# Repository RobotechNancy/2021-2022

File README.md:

**`ROBOTECH 2021-2022`** 

## **`DÉPÔT OFFICIEL`**  ##

Dépot officiel 2021-2022 de l'équipe Robotech Nancy pour le projet Coupe de France de Robotique

Après de nombreuses années à explorer les quatre coins du monde et de l’univers, nos amis les robots ont

décidé d’aller explorer leur passé. En 2022, les robots iront fouiller les ruines d’une ancienne civilisation robo-
tique à la recherche des fragments oubliés de leurs origines.

Carré de fouille, trésors enterrés et statuettes sacrées, voilà ce qui attend nos archéologues chevronnés, et
rien ne les arrêtera dans la quête de leur Histoire.
Alors sortez les pelles et les pioches, car l’aventure nous attend !

## **`Devise :`** ##
*L’utilsation optimale de l’énergie est une base élémentaire
dans l’ensemble de nos conceptions.
Savoir optimiser l’utilisation des robots existant ne nous satisfait pas.
Nous voulons apprendre à concevoir les robots de demain
utilisant des technologies novatrices ainsi qu’une 
intelligence réelle supportée par une électronique et une informatique de haut niveau.*

Nos objectifs de cette année sont :

- Construire les 2 robots nécessaires dans la version 2022 de la compétition.
- Consolider la structuration en blocs fonctionnels indépendants ( Base roulante, Odométrie, partie robotique annuelle spécifique, Introduction des services de maintenance, … ).
- Rendre les codes informatiques d’un très haut niveau de qualité ( Méthodologique, Fiables ( traitant de toutes erreurs), réelle documentation professionnelle, … ).
- Cette année nous souhaitons introduire les Graphes et moteur de Graphe afin de rendre plus facile et fiable les évolutions de la compétition tant pour cette année et surtout les années à venir.
- Introduire l’utilisation des technologies WEB dans les logiciels d’Interface Homme Robot.
- Consolider les communications hertziennes entre nos deux robots collaboratifs afin d’introduire l'immunité aux attaques de cyber-sécurité.

## **`EQUIPE DE L'ANNEE 2021-2022`**  ##

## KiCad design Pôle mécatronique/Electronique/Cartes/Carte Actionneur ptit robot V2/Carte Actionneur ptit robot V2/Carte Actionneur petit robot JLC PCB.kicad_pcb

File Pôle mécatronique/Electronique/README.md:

TO DO List:
- Base roulante
	- Cablage temp vers nucléo
	- Teste régulateur
	
- Système TOF
	- Teste des capteurs
	
- Bloc alimentation
	- Dimensionnement de la batterie
	- Dimensionnement du BMS
	- Dimensionnement du régulateur

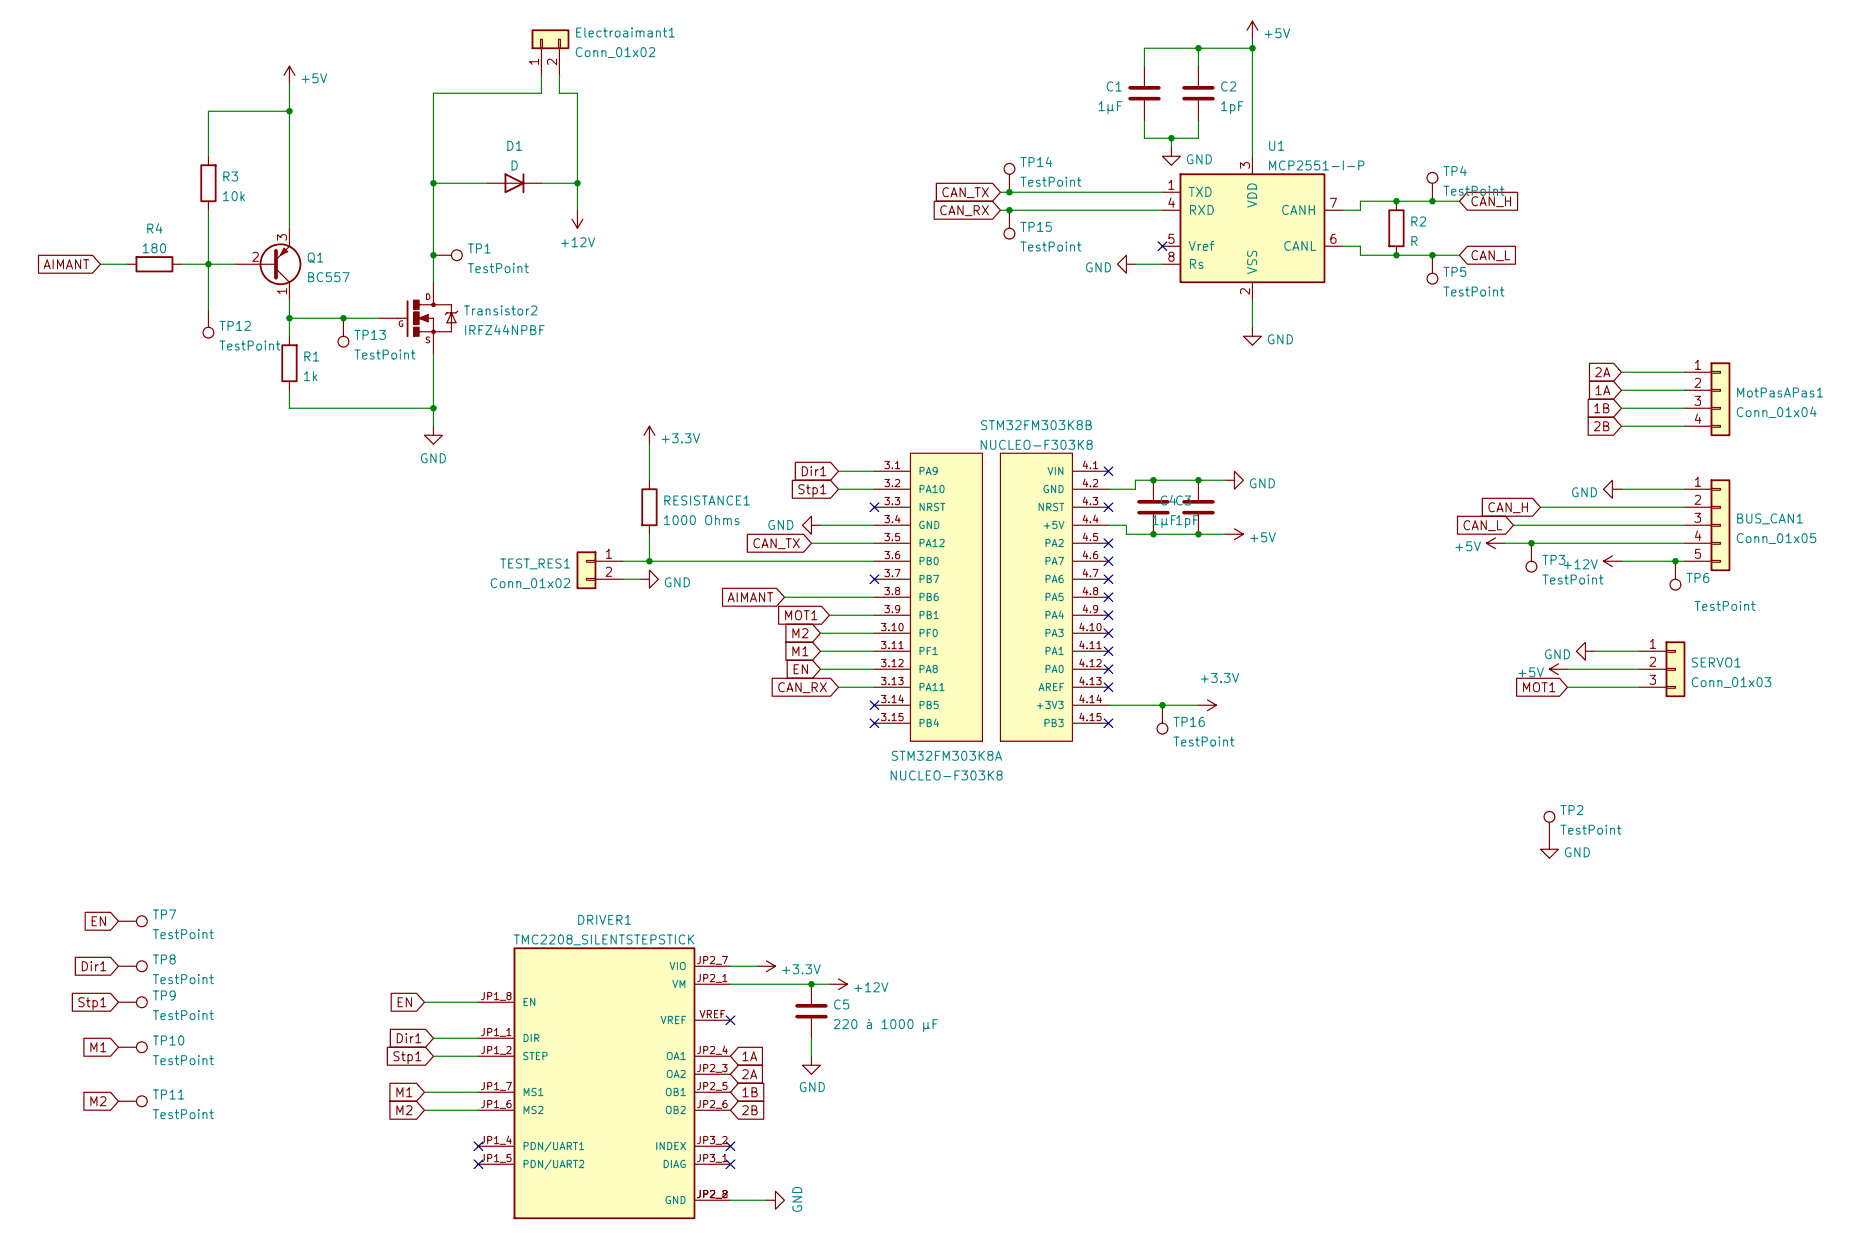
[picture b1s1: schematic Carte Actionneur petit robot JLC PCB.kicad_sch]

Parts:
BUS_CAN1: Conn_01x05; JST_PH_B5B-PH-K_1x05_P2.00mm_Vertical
C1, C4: 1µF; C_1206_3216Metric
C2, C3: 1pF; C_1206_3216Metric
C5: 220 à 1000 µF; CP_Radial_D8.0mm_P3.50mm
D1: D; D_A-405_P12.70mm_Horizontal
DRIVER1: TMC2208_SILENTSTEPSTICK; MODULE_TMC2208_SILENTSTEPSTICK
Electroaimant1: Conn_01x02; JST_PH_B2B-PH-K_1x02_P2.00mm_Vertical
MotPasAPas1: Conn_01x04; PinSocket_1x04_P2.54mm_Vertical
Q1: BC557; TO-92_Inline
R1: 1k; R_Axial_DIN0207_L6.3mm_D2.5mm_P10.16mm_Horizontal
R2: R; R_Axial_DIN0207_L6.3mm_D2.5mm_P10.16mm_Horizontal
R3: 10k; R_Axial_DIN0207_L6.3mm_D2.5mm_P10.16mm_Horizontal
R4: 180; R_Axial_DIN0207_L6.3mm_D2.5mm_P10.16mm_Horizontal
RESISTANCE1: 1000 Ohms; R_Axial_DIN0207_L6.3mm_D2.5mm_P10.16mm_Horizontal
SERVO1: Conn_01x03; JST_PH_B3B-PH-K_1x03_P2.00mm_Vertical
STM32FM303K8: NUCLEO-F303K8; iou; PARTREV 3
TEST_RES1: Conn_01x02; PinSocket_1x02_P2.54mm_Vertical
TP1, TP2, TP3, TP4, TP5, TP6, TP7, TP8, TP9, TP10, TP11, TP12, TP13, TP14, TP15, TP16: TestPoint; TestPoint_Pad_D2.0mm
Transistor2: IRFZ44NPBF; TO-220-3_Horizontal_TabDown
U1: MCP2551-I-P; DIP-8_W7.62mm

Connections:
1A: DRIVER1.JP2_4 (OA1), MotPasAPas1.2
1B: DRIVER1.JP2_5 (OB1), MotPasAPas1.3
2A: DRIVER1.JP2_3 (OA2), MotPasAPas1.1
2B: DRIVER1.JP2_6 (OB2), MotPasAPas1.4
+3V3: DRIVER1.JP2_7 (VIO), RESISTANCE1.1, STM32FM303K8.4.14 (+3V3), TP16.1
+5V: BUS_CAN1.4, C1.1, C2.1, C3.2, C4.2, Q1.3 (E), R3.2, SERVO1.2, STM32FM303K8.4.4 (+5V), TP3.1, U1.3 (VDD)
+12V: BUS_CAN1.5, C5.1, D1.1 (K), DRIVER1.JP2_1 (VM), Electroaimant1.2, TP6.1
AIMANT: R4.2, STM32FM303K8.3.8 (PB6)
CAN_H: BUS_CAN1.2, R2.1, TP4.1, U1.7 (CANH)
CAN_L: BUS_CAN1.3, R2.2, TP5.1, U1.6 (CANL)
CAN_RX: STM32FM303K8.3.13 (PA11), TP15.1, U1.4 (RXD)
CAN_TX: STM32FM303K8.3.5 (PA12), TP14.1, U1.1 (TXD)
Dir1: DRIVER1.JP1_1 (DIR), STM32FM303K8.3.1 (PA9), TP8.1
EN: DRIVER1.JP1_8 (EN), STM32FM303K8.3.12 (PA8), TP7.1
GND: BUS_CAN1.1, C1.2, C2.2, C3.1, C4.1, C5.2, DRIVER1.JP2_2 (GND), DRIVER1.JP2_8 (GND), R1.1, SERVO1.1, STM32FM303K8.3.4 (GND), STM32FM303K8.4.2 (GND), TEST_RES1.2, TP2.1, Transistor2.3, U1.2 (VSS), U1.8 (Rs)
M1: DRIVER1.JP1_7 (MS1), STM32FM303K8.3.11 (PF1), TP10.1
M2: DRIVER1.JP1_6 (MS2), STM32FM303K8.3.10 (PF0), TP11.1
MOT1: SERVO1.3, STM32FM303K8.3.9 (PB1)
unnamed: D1.2 (A), Electroaimant1.1, TP1.1, Transistor2.2
unnamed: Q1.1 (C), R1.2, TP13.1, Transistor2.1
unnamed: Q1.2 (B), R3.1, R4.1, TP12.1
unnamed: RESISTANCE1.2, STM32FM303K8.3.6 (PB0), TEST_RES1.1
Stp1: DRIVER1.JP1_2 (STEP), STM32FM303K8.3.2 (PA10), TP9.1

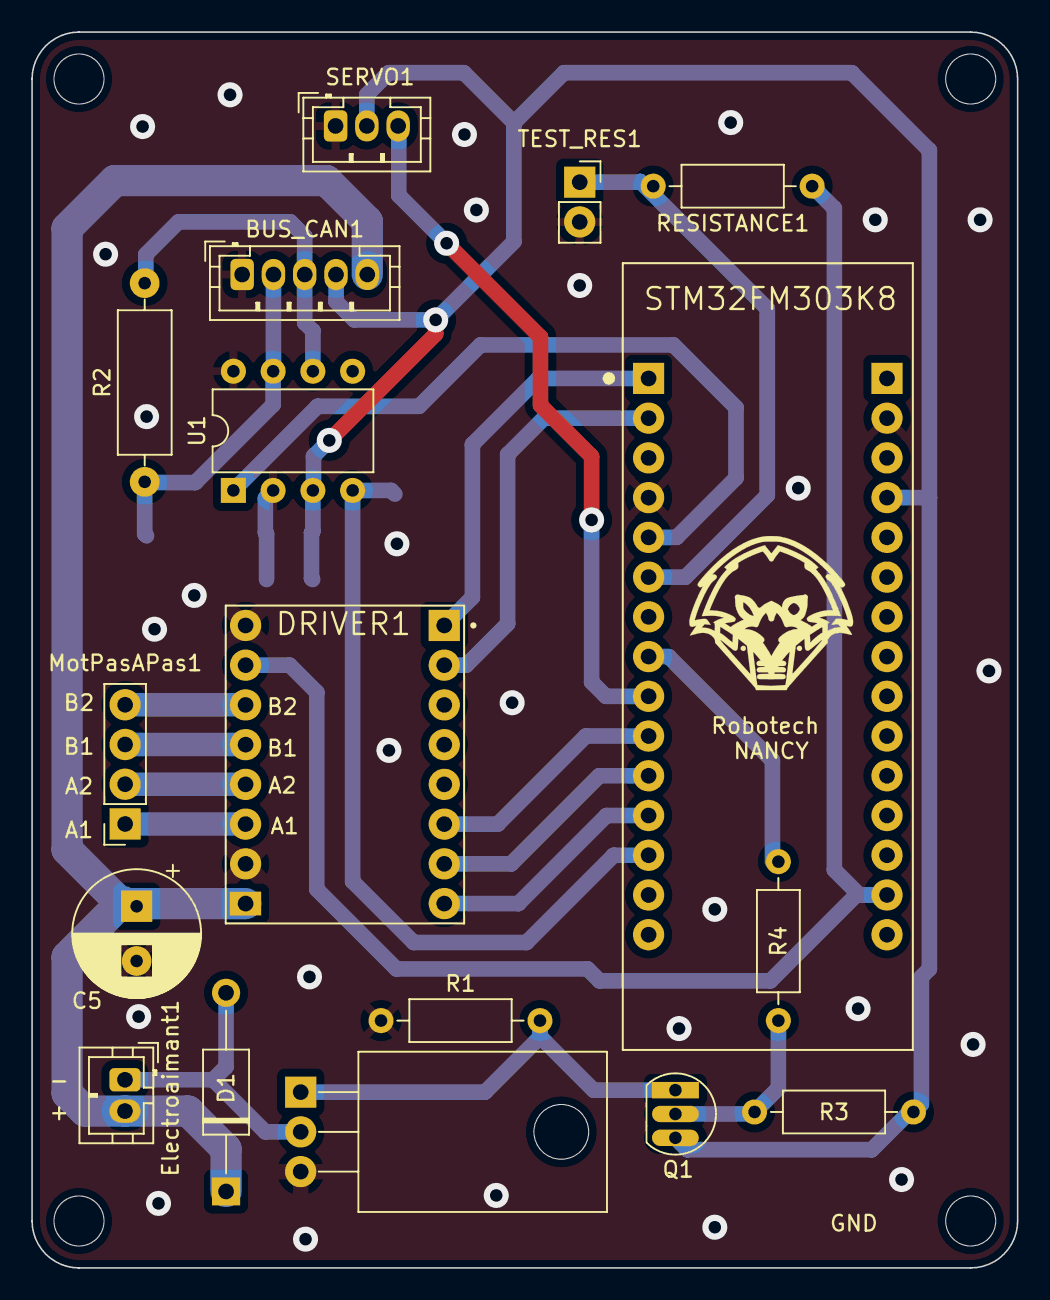
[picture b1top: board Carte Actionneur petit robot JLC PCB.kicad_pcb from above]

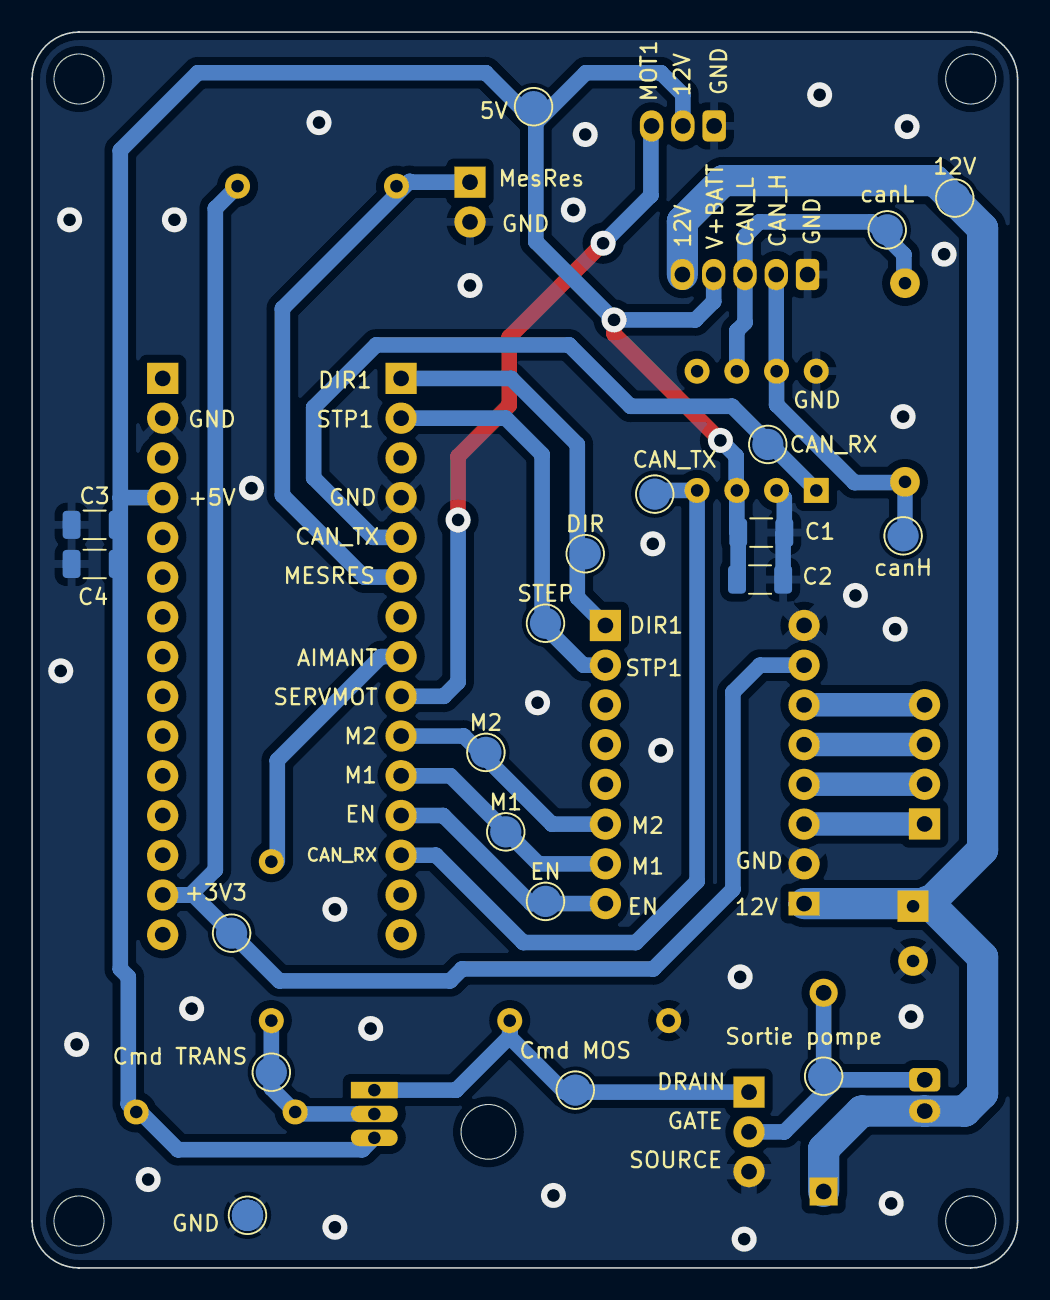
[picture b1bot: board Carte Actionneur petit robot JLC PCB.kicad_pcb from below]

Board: 2 copper layers, 63.0 x 79.0 mm, 37 parts (20 on the bottom side), 23 nets.

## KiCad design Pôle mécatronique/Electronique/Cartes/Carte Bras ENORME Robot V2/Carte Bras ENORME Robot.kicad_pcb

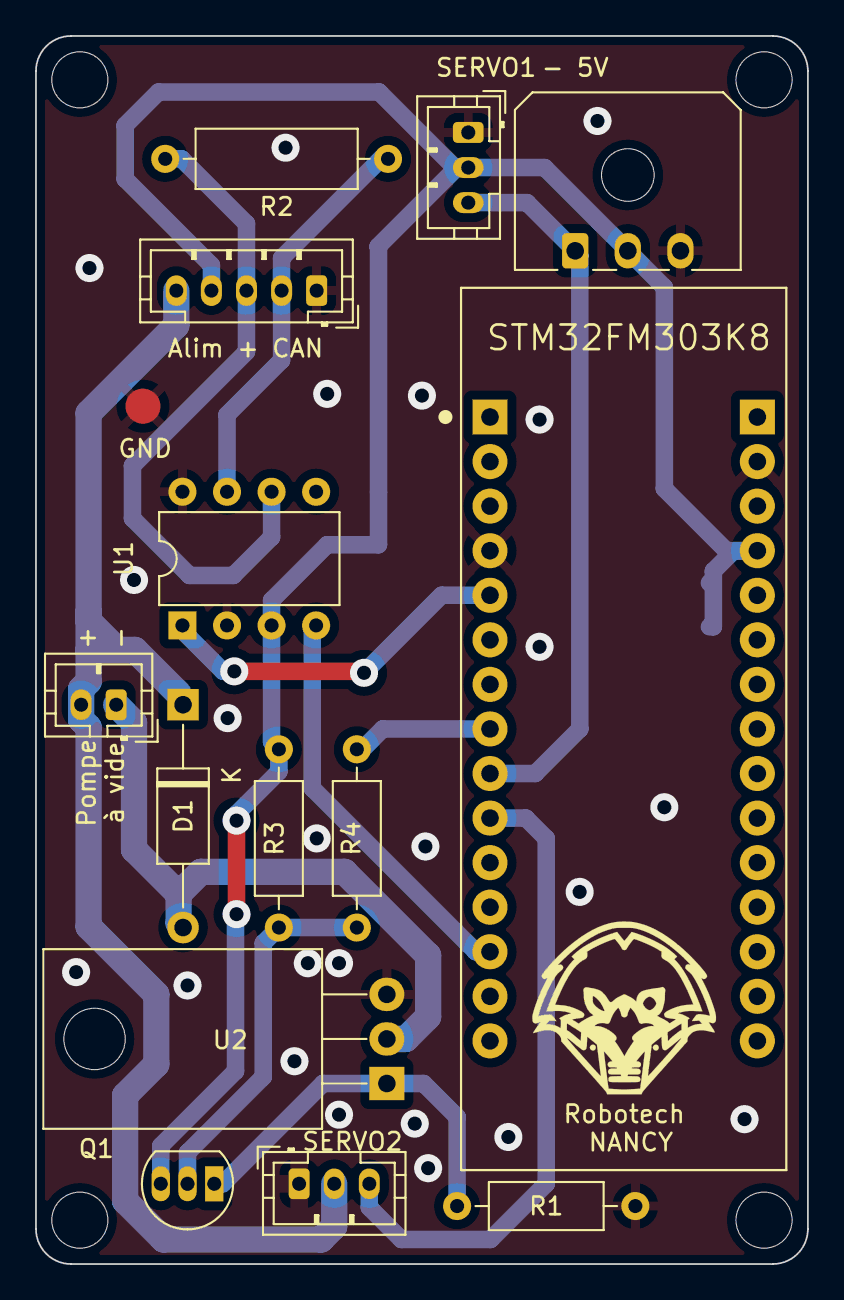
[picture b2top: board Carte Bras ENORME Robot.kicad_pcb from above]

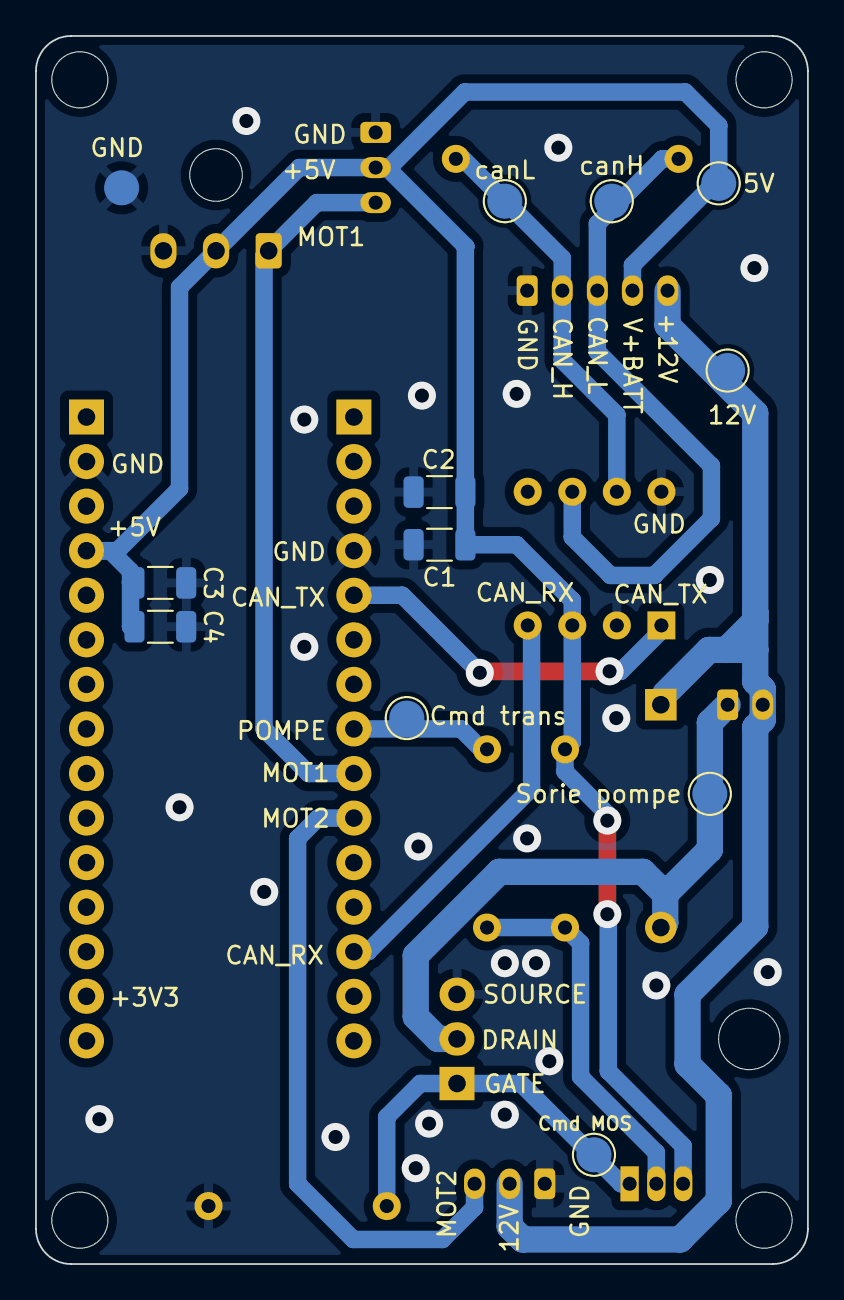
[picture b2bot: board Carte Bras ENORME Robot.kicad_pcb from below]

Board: 2 copper layers, 44.0 x 70.0 mm, 25 parts (11 on the bottom side), 13 nets.

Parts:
BUS_CAN1: Conn_01x05; JST_PH_B5B-PH-K_1x05_P2.00mm_Vertical
C1, C2, C3, C4: C; C_1206_3216Metric
D1: D; D_A-405_P12.70mm_Horizontal
JS1: Molex_Micro-Fit_3.0_43650-0300_1x03_P3.00mm_Horiz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; Molex_Micro-Fit_3.0_43650-0300_1x03_P3.00mm_Horizontal
PompeAVide1: Conn_01x02; JST_PH_B2B-PH-K_1x02_P2.00mm_Vertical
Q1: BC557; TO-92_Inline
R1: 1k; R_Axial_DIN0207_L6.3mm_D2.5mm_P10.16mm_Horizontal
R2: R; R_Axial_DIN0309_L9.0mm_D3.2mm_P12.70mm_Horizontal
R3: 10k; R_Axial_DIN0207_L6.3mm_D2.5mm_P10.16mm_Horizontal
R4: 180; R_Axial_DIN0207_L6.3mm_D2.5mm_P10.16mm_Horizontal
SERVO1, SERVO2: Conn_01x03; JST_PH_B3B-PH-K_1x03_P2.00mm_Vertical
STM32FM303K8: NUCLEO-F303K8; MODULE_NUCLEO-F303K8
TP2, TP3, TP4, TP5, TP6, TP7, TP8: TestPoint; TestPoint_Pad_D2.0mm
U1: MCP2551-I-P; DIP-8_W7.62mm
U2: IRFZ44NPBF; TO-220-3_Horizontal_TabDown

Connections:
+5V: BUS_CAN1.4, C1.1, C2.1, C3.2, C4.2, JS1.2, Q1.3 (E), R3.1, SERVO1.2, STM32FM303K8.4.4 (+5V), TP3.1, U1.3 (VDD)
+12V: BUS_CAN1.5, D1.1 (K), PompeAVide1.2, SERVO2.2, TP6.1
CAN_H: BUS_CAN1.2, R2.1, TP4.1, U1.7 (CANH)
CAN_L: BUS_CAN1.3, R2.2, TP5.1, U1.6 (CANL)
CAN_RX: STM32FM303K8.3.13 (PA11), U1.4 (RXD)
CAN_TX: STM32FM303K8.3.5 (PA12), U1.1 (TXD)
GND: BUS_CAN1.1, C1.2, C2.2, C3.1, C4.1, JS1.3, R1.2, SERVO1.1, SERVO2.1, STM32FM303K8.3.4 (GND), STM32FM303K8.4.2 (GND), U1.2 (VSS), U1.8 (Rs), U2.3
MOT1: JS1.1, SERVO1.3, STM32FM303K8.3.9 (PB1)
MOT2: SERVO2.3, STM32FM303K8.3.10 (PF0)
unnamed: D1.2 (A), PompeAVide1.1, TP2.1, U2.2
unnamed: Q1.1 (C), R1.1, TP8.1, U2.1
unnamed: Q1.2 (B), R3.2, R4.2
POMPE: R4.1, STM32FM303K8.3.8 (PB6), TP7.1

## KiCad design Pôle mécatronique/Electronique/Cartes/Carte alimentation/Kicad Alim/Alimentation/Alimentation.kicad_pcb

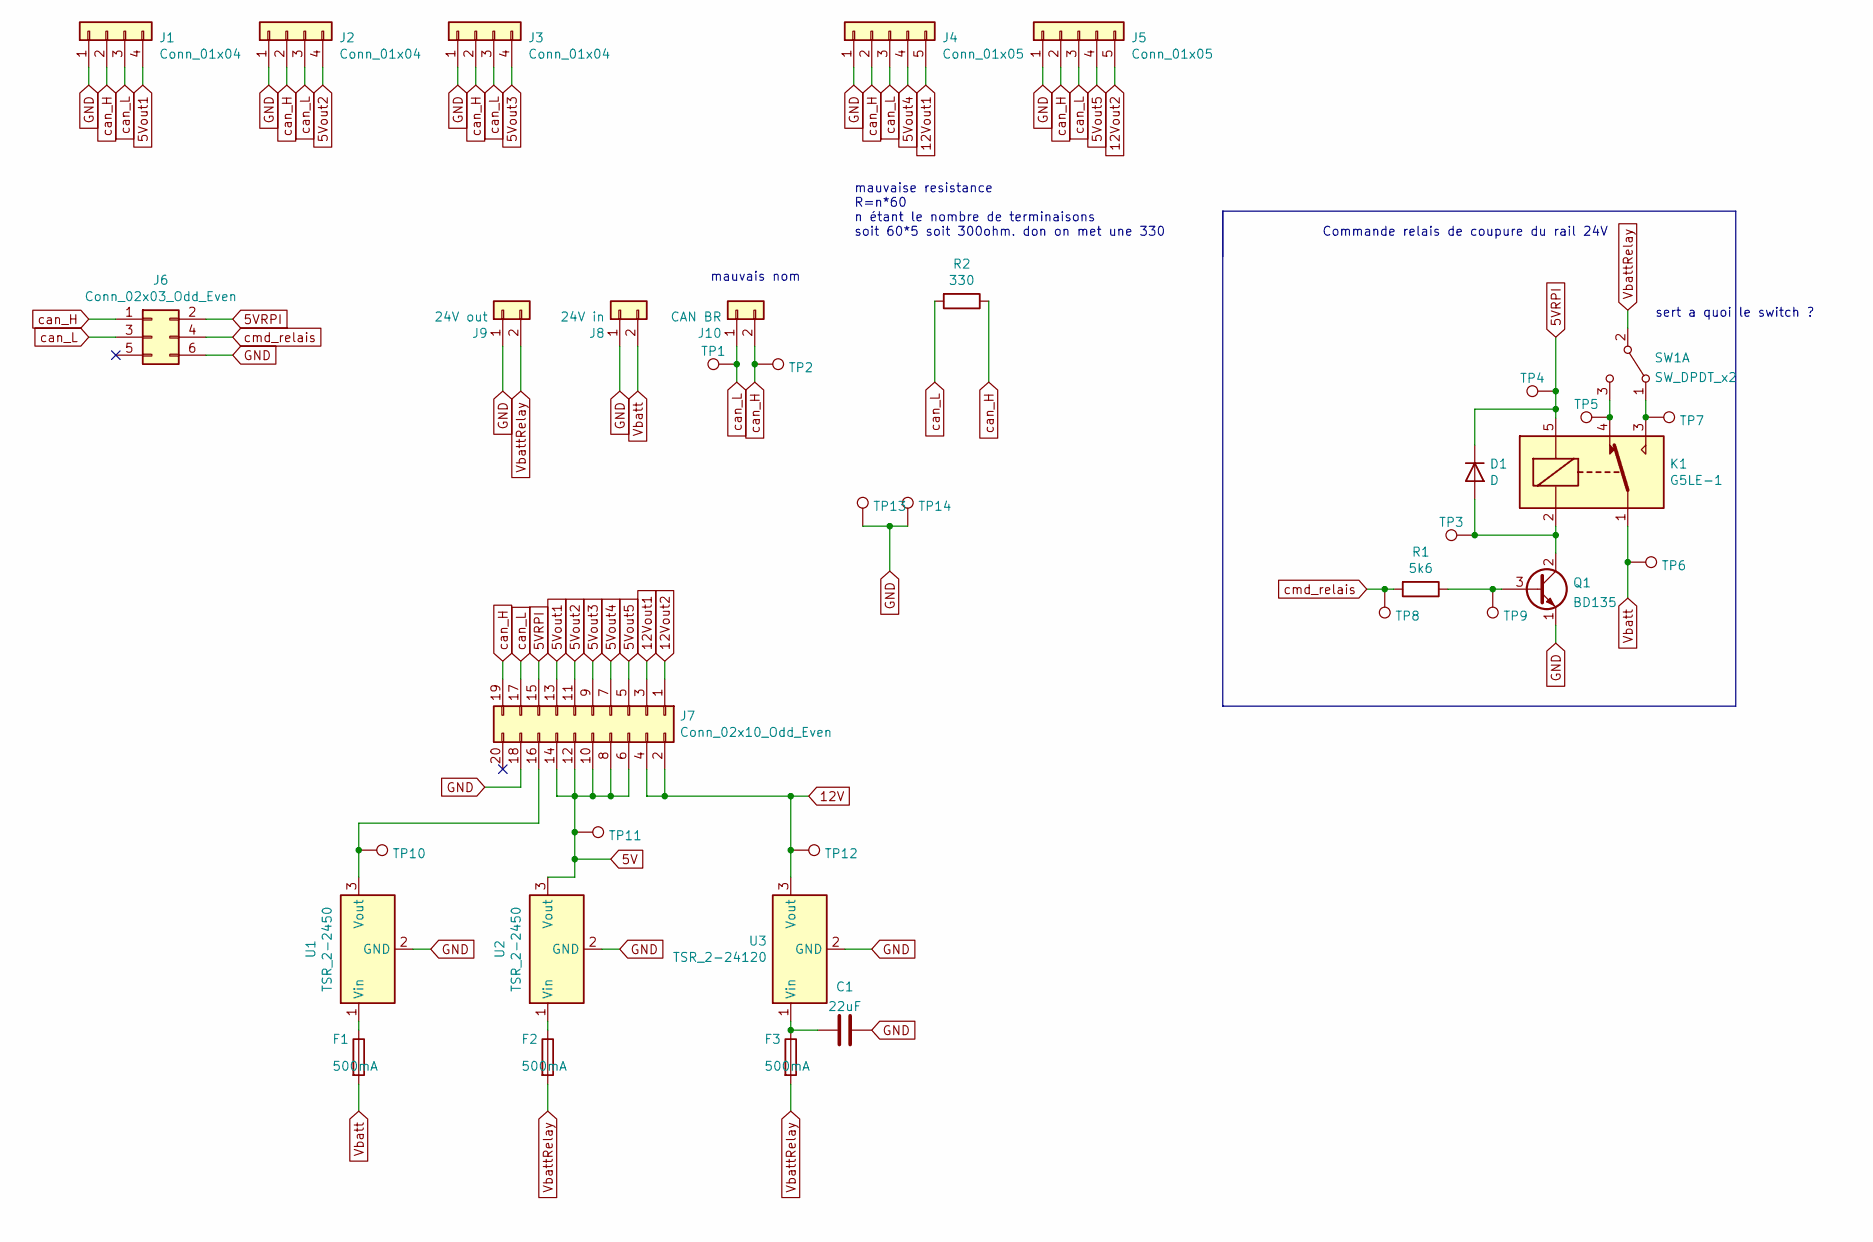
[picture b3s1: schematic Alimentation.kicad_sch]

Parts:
C1: 22uF; CP_Radial_D5.0mm_P2.00mm
D1: D; D_DO-15_P12.70mm_Horizontal
F1, F2, F3: 500mA; Fuse_BelFuse_0ZRE0012FF_L8.3mm_W3.8mm
J1, J2, J3: Conn_01x04; JST_PH_B4B-PH-K_1x04_P2.00mm_Vertical
J4, J5: Conn_01x05; JST_PH_B5B-PH-K_1x05_P2.00mm_Vertical
J6: Conn_02x03_Odd_Even; Hirose_DF11-6DP-2DSA_2x03_P2.00mm_Vertical
J7: Conn_02x10_Odd_Even; PinSocket_2x10_P2.54mm_Vertical
J8: 24V in; AMASS_XT60-F_1x02_P7.20mm_Vertical
J9: 24V out; AMASS_XT60-F_1x02_P7.20mm_Vertical
J10: CAN BR; JST_PH_B2B-PH-K_1x02_P2.00mm_Vertical
K1: G5LE-1; Relay_SPDT_Omron-G5LE-1
Q1: BD135; TO-126-3_Vertical
R1: 5k6; R_Axial_DIN0207_L6.3mm_D2.5mm_P10.16mm_Horizontal
R2: 330; R_Axial_DIN0207_L6.3mm_D2.5mm_P10.16mm_Horizontal
SW1: SW_DPDT_x2; Switch_3_Pin
TP1, TP2, TP3, TP4, TP5, TP6, TP7, TP8, TP9, TP10, TP11, TP12, TP13, TP14: TestPoint; TestPoint_Pad_D2.0mm
U1, U2: TSR_2-2450; Converter_DCDC_TRACO_TSR-1_THT
U3: TSR_2-24120; Converter_DCDC_TRACO_TSR-1_THT

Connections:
5V: J7.6, J7.8, J7.10, J7.12, J7.14, TP11.1, U2.3 (Vout)
5VRPI: D1.1 (K), J6.2, J7.15, K1.5, TP4.1
5Vout1: J1.4, J7.13
5Vout2: J2.4, J7.11
5Vout3: J3.4, J7.9
5Vout4: J4.4, J7.7
5Vout5: J5.4, J7.5
12V: J7.2, J7.4, TP12.1, U3.3 (Vout)
12Vout1: J4.5, J7.3
12Vout2: J5.5, J7.1
GND: C1.2, J1.1, J2.1, J3.1, J4.1, J5.1, J6.6, J7.18, J8.1, J9.1, Q1.1 (E), TP13.1, TP14.1, U1.2 (GND), U2.2 (GND), U3.2 (GND)
unnamed: C1.1, F3.1, U3.1 (Vin)
unnamed: D1.2 (A), K1.2, Q1.2 (C), TP3.1
unnamed: F1.1, U1.1 (Vin)
unnamed: F2.1, U2.1 (Vin)
unnamed: J7.16, TP10.1, U1.3 (Vout)
unnamed: K1.3, SW1.1 (A), TP7.1
unnamed: K1.4, SW1.3 (C), TP5.1
unnamed: Q1.3 (B), R1.1, TP9.1
Vbatt: F1.2, J8.2, K1.1, TP6.1
VbattRelay: F2.2, F3.2, J9.2, SW1.2 (B)
can_H: J1.2, J2.2, J3.2, J4.2, J5.2, J6.1, J7.19, J10.2, R2.1, TP2.1
can_L: J1.3, J2.3, J3.3, J4.3, J5.3, J6.3, J7.17, J10.1, R2.2, TP1.1
cmd_relais: J6.4, R1.2, TP8.1

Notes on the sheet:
Commande relais de coupure du rail 24V
mauvaise resistance R=n*60 n étant le nombre de terminaisons soit 60*5 soit 300ohm. don on met une 330
sert a quoi le switch ?
mauvais nom

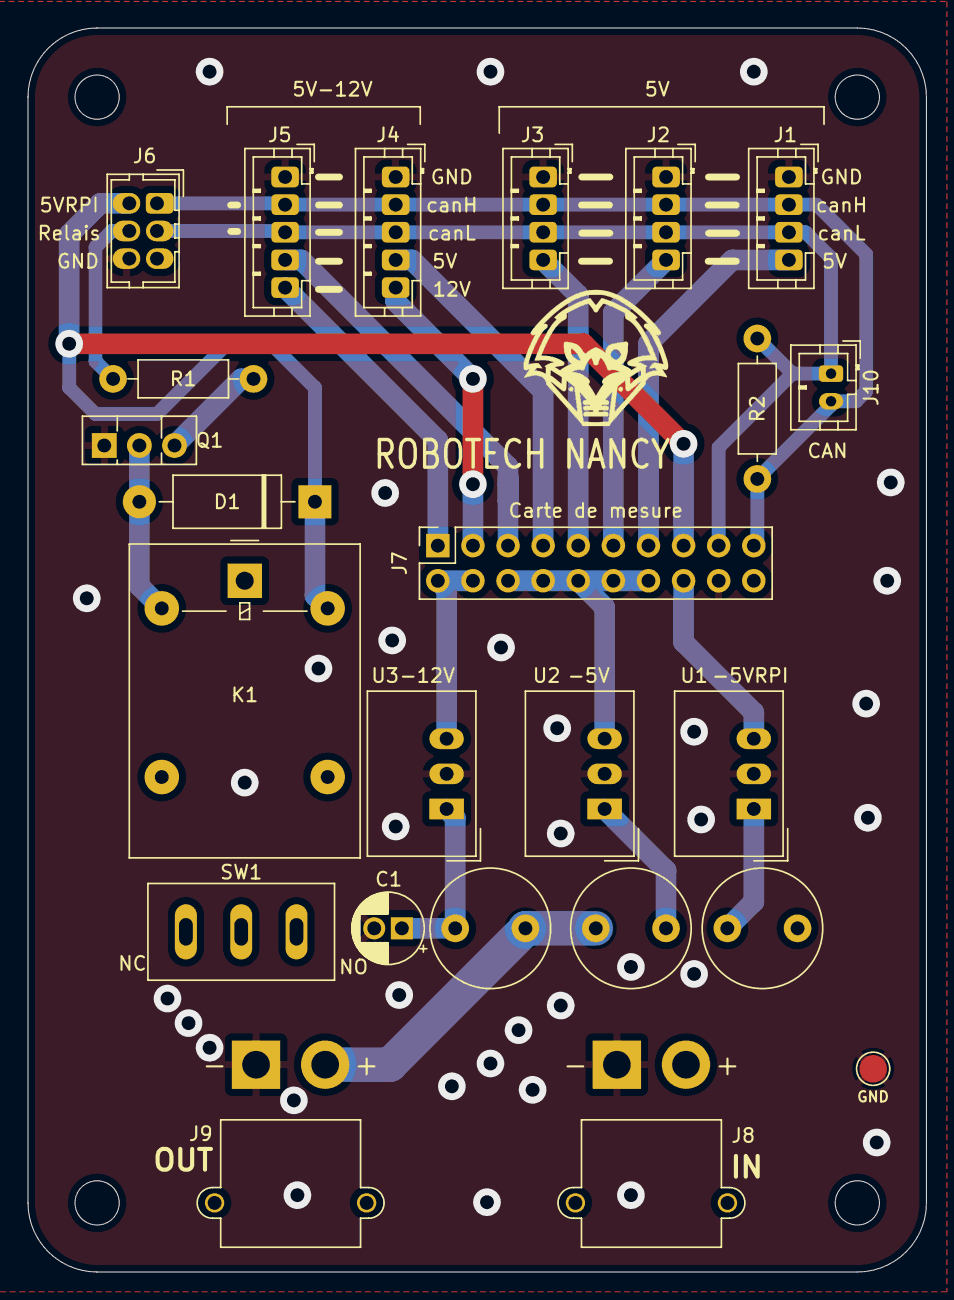
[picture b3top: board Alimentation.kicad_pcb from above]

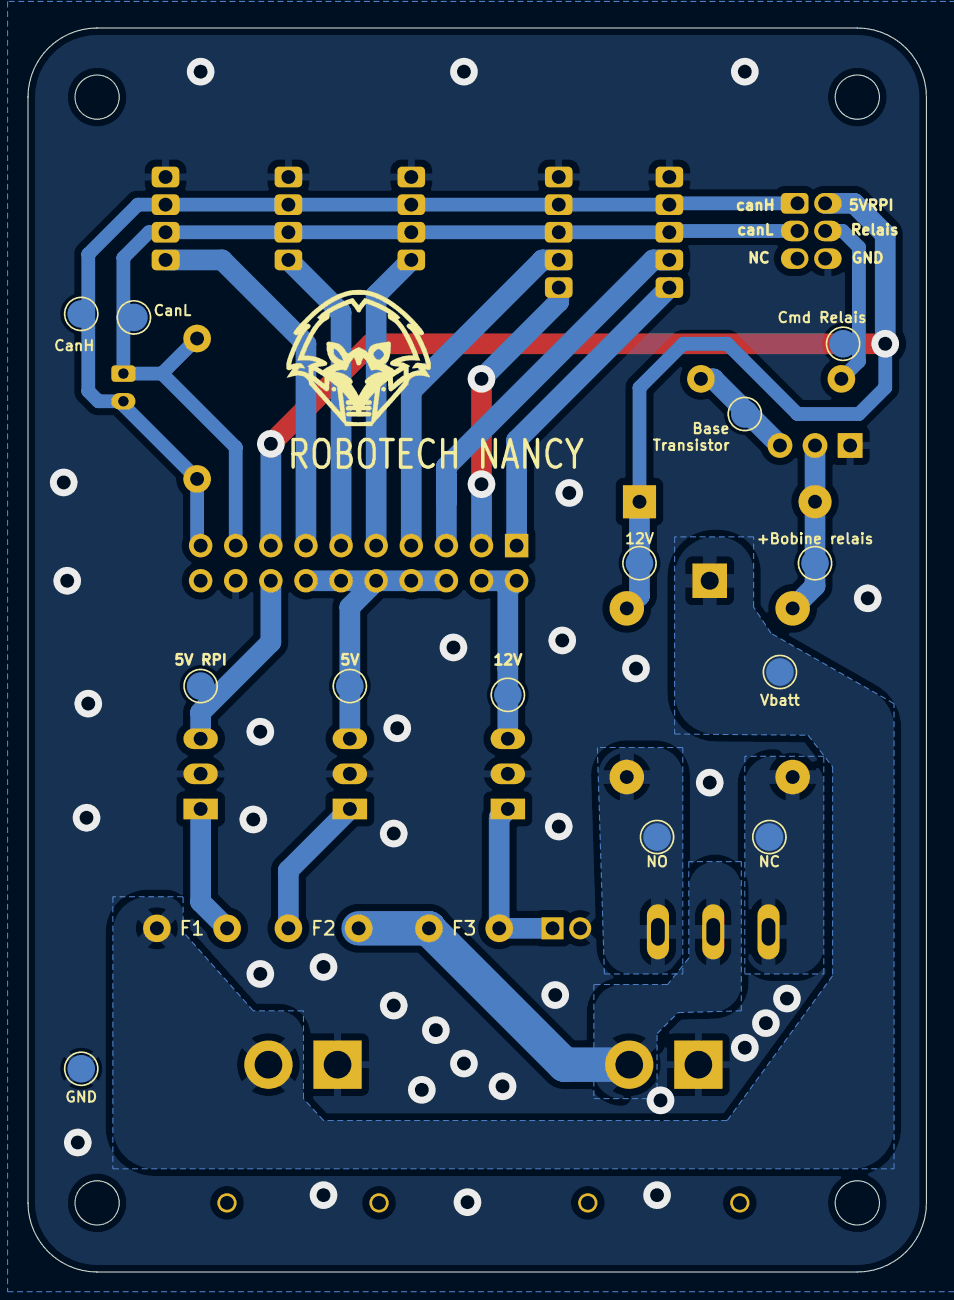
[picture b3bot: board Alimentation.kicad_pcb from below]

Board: 2 copper layers, 65.0 x 90.0 mm, 37 parts (13 on the bottom side), 24 nets.

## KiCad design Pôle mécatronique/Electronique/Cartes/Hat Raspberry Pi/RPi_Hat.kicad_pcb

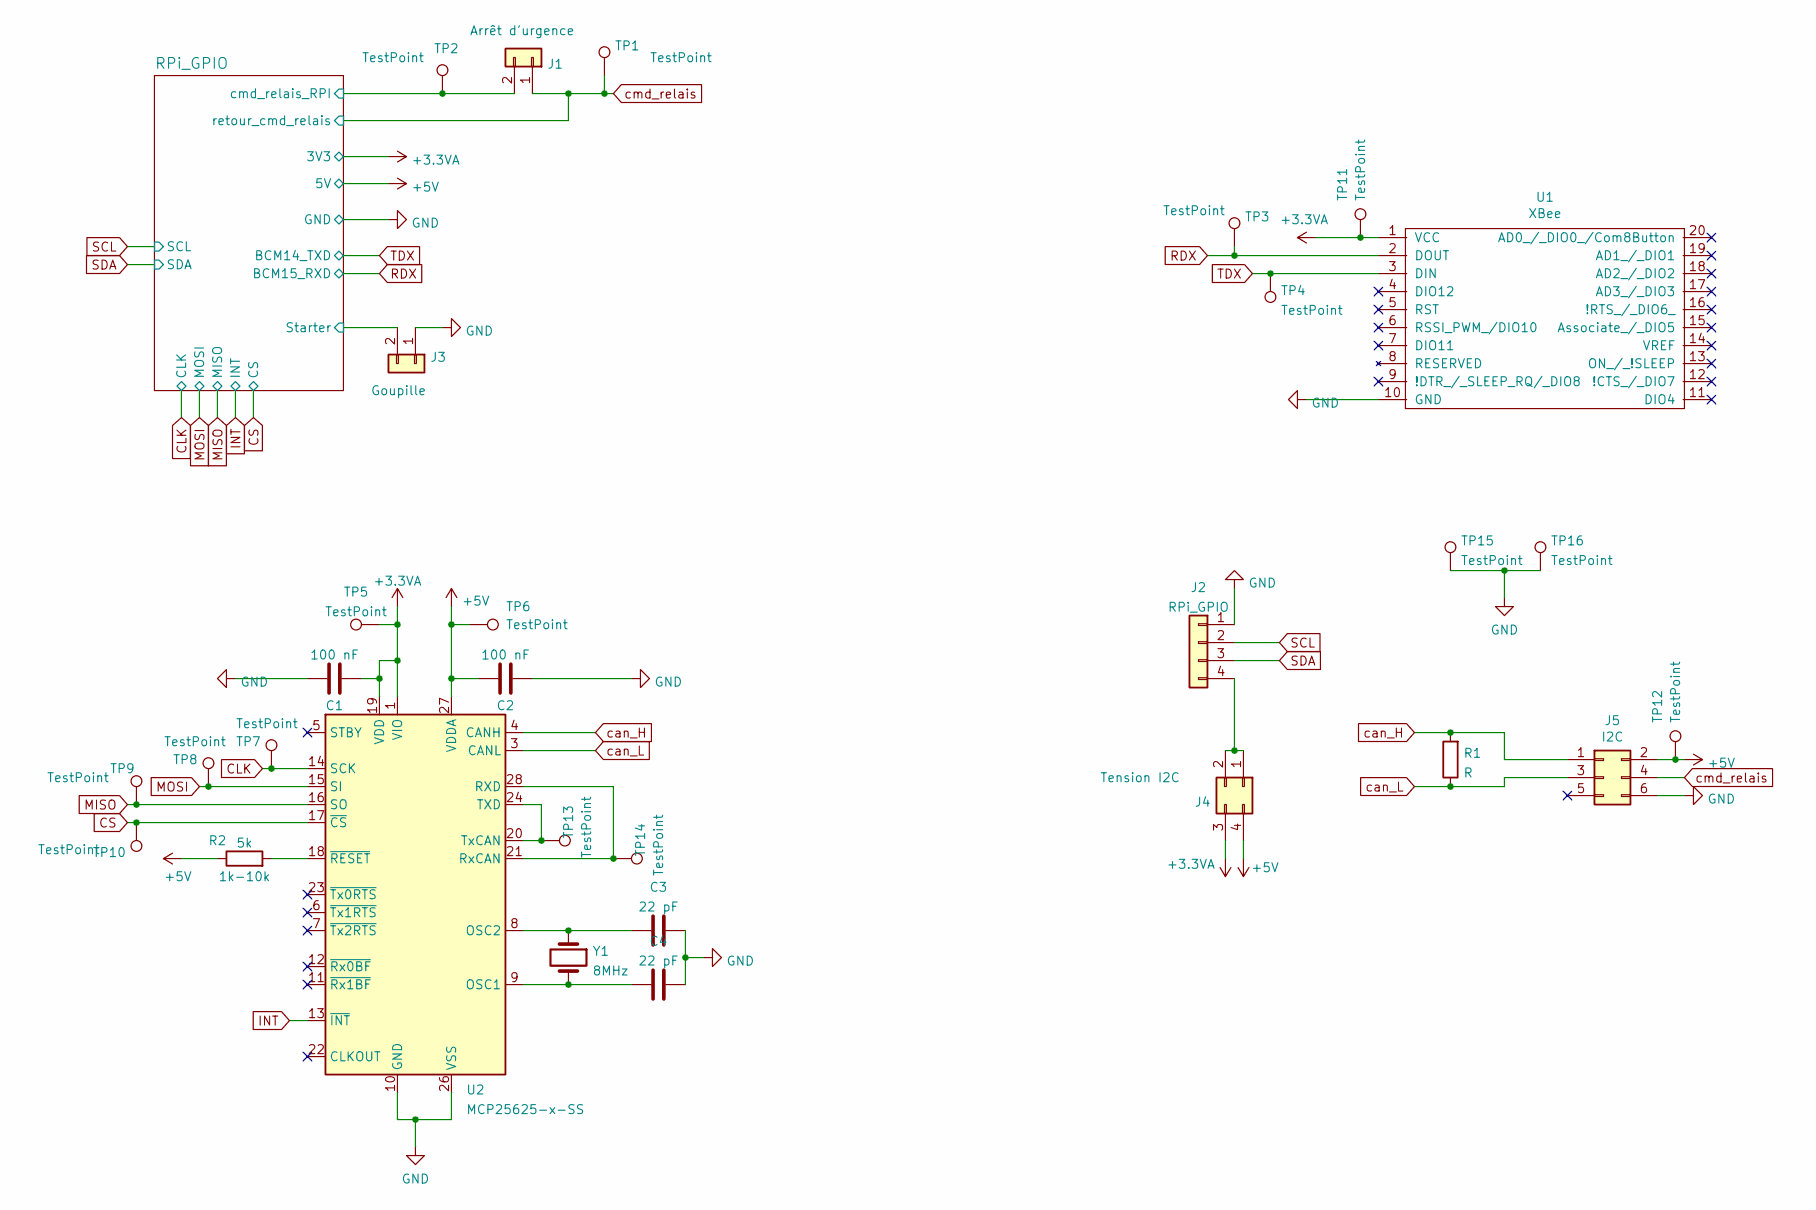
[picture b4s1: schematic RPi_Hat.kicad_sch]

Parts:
C1, C2: 100 nF; C_Disc_D5.1mm_W3.2mm_P5.00mm
C3, C4: 22 pF; C_Disc_D5.1mm_W3.2mm_P5.00mm
J1: Arrêt d'urgence; Hirose_DF11-6DP-2DSA_2x03_P2.00mm_Vertical
J2: RPi_GPIO; Pin_Header_Straight_2x20
J3: Goupille; JST_PH_B2B-PH-K_1x02_P2.00mm_Vertical
J4: Tension I2C; JST_PH_B2B-PH-K_1x02_P2.00mm_Vertical
J5: I2C; JST_PH_B4B-PH-K_1x04_P2.00mm_Vertical
R1: R; R_Axial_DIN0207_L6.3mm_D2.5mm_P2.54mm_Vertical
R2: 5k; R_Axial_DIN0207_L6.3mm_D2.5mm_P10.16mm_Horizontal
TP1, TP2, TP3, TP4, TP5, TP6, TP7, TP8, TP9, TP10, TP11, TP12, TP13, TP14: TestPoint; TestPoint_Pad_D1.0mm
TP15, TP16: TestPoint; TestPoint_Pad_D2.0mm
U1: XBee; XBEE-20_THT
U2: MCP25625-x-SS; SSOP-28_5.3x10.2mm_P0.65mm
Y1: 8MHz; Crystal_HC50_Horizontal

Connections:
+3.3VA: C1.2, J4.3, TP5.1, TP11.1, U1.1 (VCC), U2.1 (VIO), U2.19 (VDD); also elsewhere on the board
+5V: C2.1, J4.4, J5.2, R2.1, TP6.1, TP12.1, U2.27 (VDDA); also elsewhere on the board
/RPi_GPIO/BCM14_TXD: TP4.1, U1.3 (DIN); also elsewhere on the board
/RPi_GPIO/BCM15_RXD: TP3.1, U1.2 (DOUT); also elsewhere on the board
/RPi_GPIO/Starter: J3.2; also elsewhere on the board
/RPi_GPIO/cmd_relais_RPI: J1.2, TP2.1; also elsewhere on the board
CLK: TP7.1, U2.14 (SCK); also elsewhere on the board
CS: TP10.1, U2.17 (~CS); also elsewhere on the board
GND: C1.1, C2.2, C3.2, C4.2, J2.1, J3.1, J5.6, TP15.1, TP16.1, U1.10 (GND), U2.10 (GND), U2.26 (VSS); also elsewhere on the board
INT: U2.13 (~INT); also elsewhere on the board
MISO: TP9.1, U2.16 (SO); also elsewhere on the board
MOSI: TP8.1, U2.15 (SI); also elsewhere on the board
unnamed: C3.1, U2.8 (OSC2), Y1.1
unnamed: C4.1, U2.9 (OSC1), Y1.2
unnamed: J2.4, J4.1, J4.2
unnamed: R2.2, U2.18 (~RESET)
unnamed: TP13.1, U2.20 (TxCAN), U2.24 (TXD)
unnamed: TP14.1, U2.21 (RxCAN), U2.28 (RXD)
SCL: J2.2; also elsewhere on the board
SDA: J2.3; also elsewhere on the board
can_H: J5.1, R1.2, U2.4 (CANH)
can_L: J5.3, R1.1, U2.3 (CANL)
cmd_relais: J1.1, J5.4, TP1.1; also elsewhere on the board

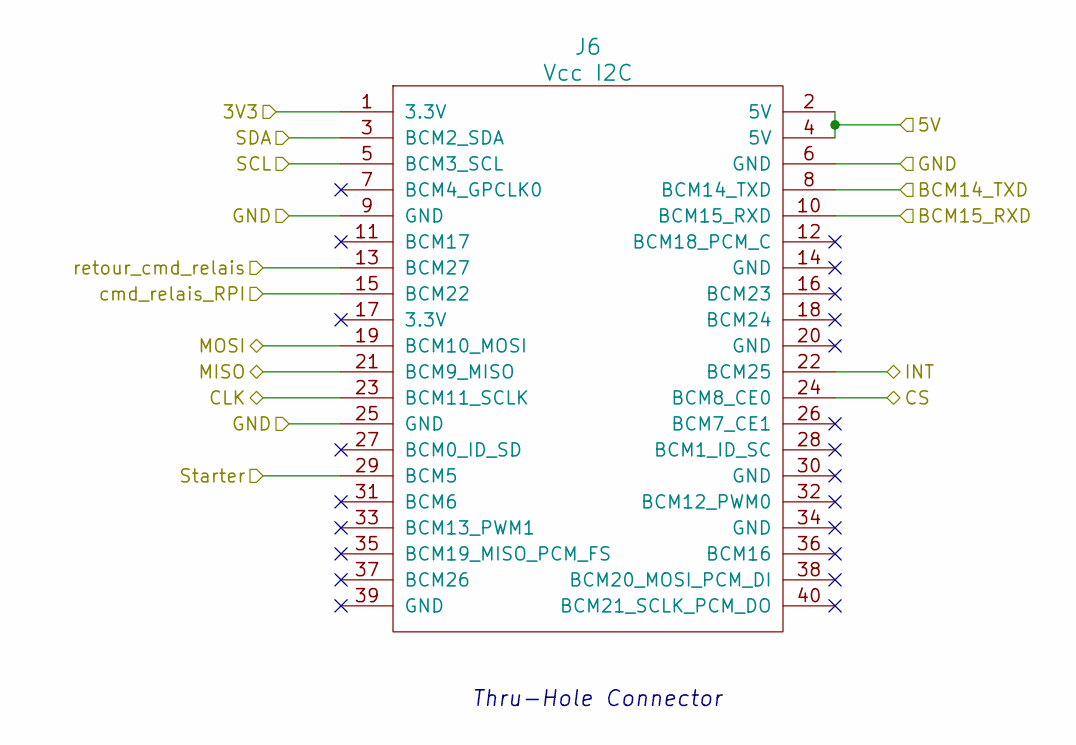
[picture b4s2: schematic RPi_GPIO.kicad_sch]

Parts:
J6: Vcc I2C; PinHeader_2x02_P2.54mm_Vertical

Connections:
+3.3VA: J6.1 (3.3V); also elsewhere on the board
+5V: J6.2 (5V), J6.4 (5V); also elsewhere on the board
/RPi_GPIO/BCM14_TXD: J6.8 (BCM14_TXD); also elsewhere on the board
/RPi_GPIO/BCM15_RXD: J6.10 (BCM15_RXD); also elsewhere on the board
/RPi_GPIO/Starter: J6.29 (BCM5); also elsewhere on the board
/RPi_GPIO/cmd_relais_RPI: J6.15 (BCM22); also elsewhere on the board
CLK: J6.23 (BCM11_SCLK); also elsewhere on the board
CS: J6.24 (BCM8_CE0); also elsewhere on the board
GND: J6.6 (GND), J6.9 (GND), J6.25 (GND); also elsewhere on the board
INT: J6.22 (BCM25); also elsewhere on the board
MISO: J6.21 (BCM9_MISO); also elsewhere on the board
MOSI: J6.19 (BCM10_MOSI); also elsewhere on the board
SCL: J6.5 (BCM3_SCL); also elsewhere on the board
SDA: J6.3 (BCM2_SDA); also elsewhere on the board
cmd_relais: J6.13 (BCM27); also elsewhere on the board

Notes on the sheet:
Thru-Hole Connector
